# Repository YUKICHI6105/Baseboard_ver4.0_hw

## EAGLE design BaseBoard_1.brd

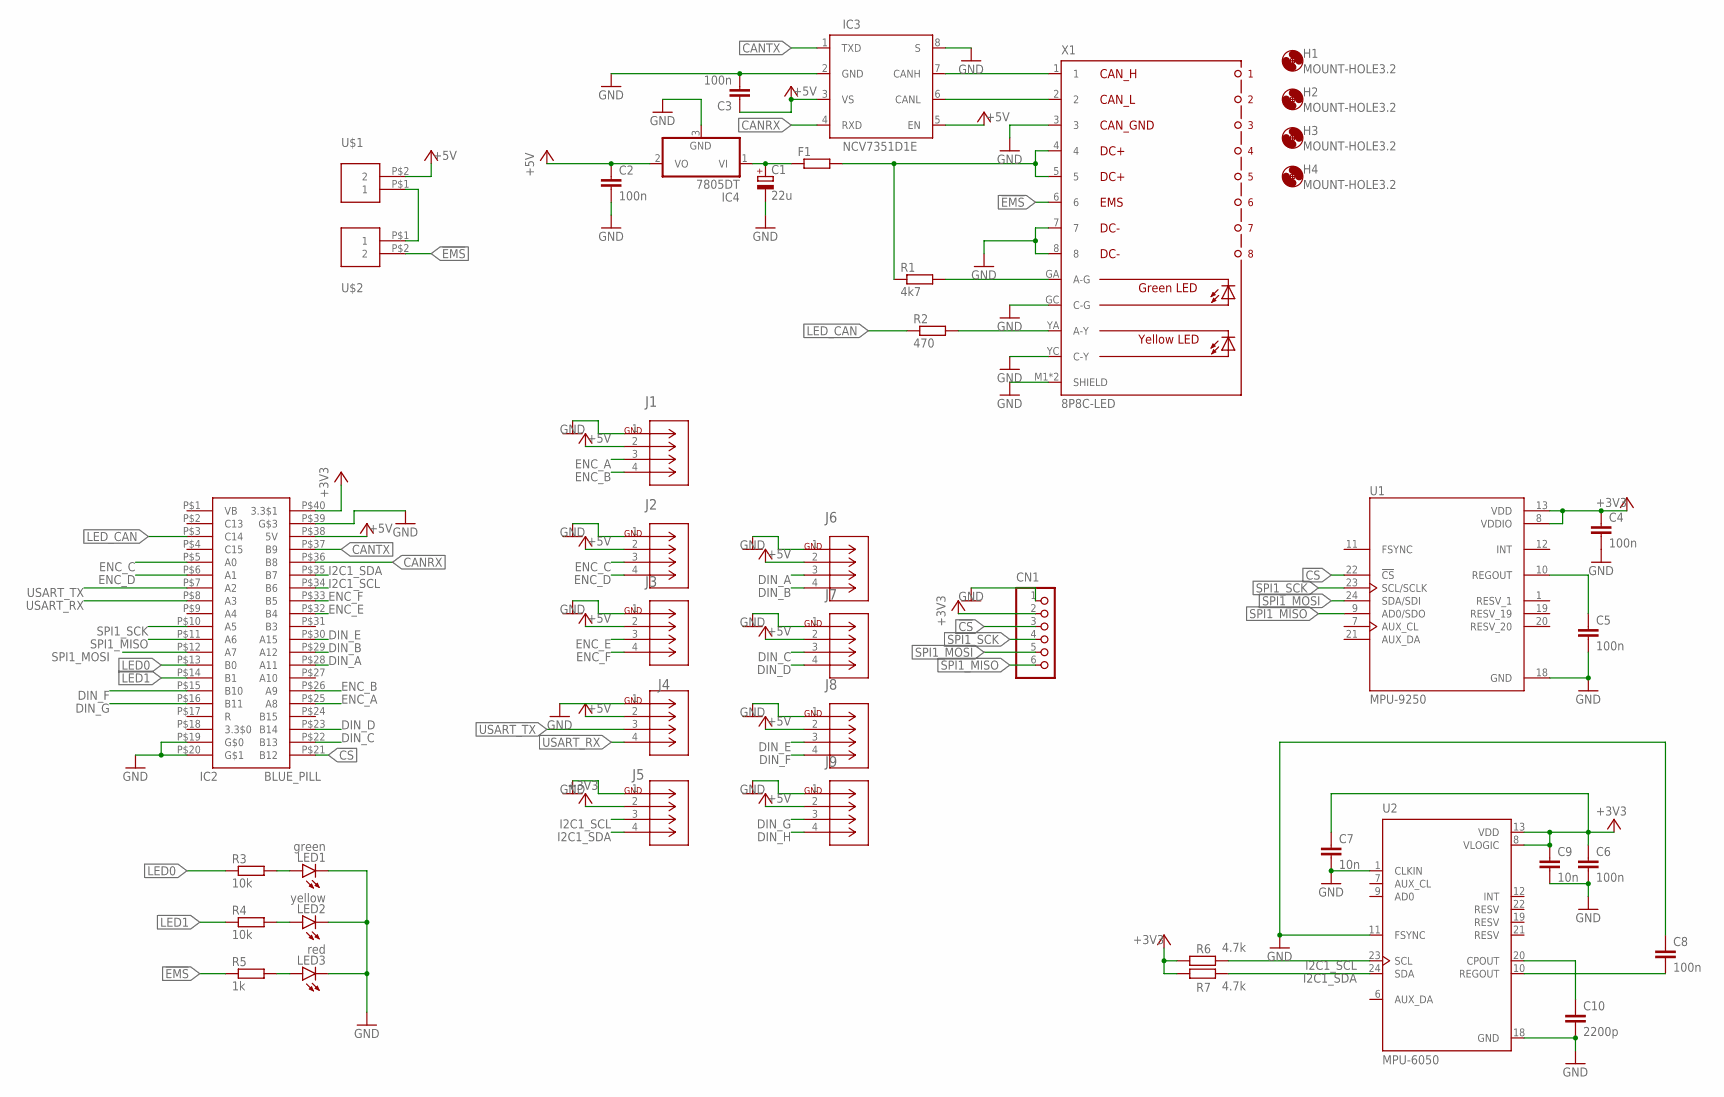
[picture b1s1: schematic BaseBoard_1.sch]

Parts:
C1: 22u; E2,5-5
C2, C3, C4, C5, C6, C8: 100n; C0603
C7, C9: 10n; C0603
C10: 2200p; C0603
CN1: S6B-XH-A
F1: R-EU_R1206; R1206
H1, H2, H3, H4: MOUNT-HOLE3.2; 3,2
IC2: BLUE_PILL
IC3: NCV7351D1E; SO08
IC4: 7805DT; TO252
J1, J2, J3, J4, J5, J6, J7, J8, J9: EP2.5-4-SIDE; CONN4_1744426-4
LED1: green; CHIPLED_0805
LED2: yellow; CHIPLED_0805
LED3: red; CHIPLED_0805
R1: 4k7; R0603
R2: 470; R0603
R3, R4: 10k; R0603
R5: 1k; R0603
R6, R7: 4.7k; R0603
U1: MPU-9250; QFN40P300X300X105-24N
U2: MPU-6050; QFN50P400X400X95-24N
U$1, U$2: XH-2-STRAIGHT; CON-XH-2-STRAIGHT
X1: 8P8C-LED

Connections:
!CS: CN1.3, IC2.P$21 (B12), U1.22 (!CS)
!EMS: R5.1, U$2.P$2 (2), X1.6
+3V3: C4.1, C6.1, C7.1, C9.1, CN1.2, IC2.P$40 (3.3$1), J5.2, R6.1, R7.1, U1.8 (VDDIO), U1.13 (VDD), U2.8 (VLOGIC), U2.13 (VDD)
+5V: C2.1, C3.1, IC2.P$38 (5V), IC3.3 (VS), IC3.5 (EN), IC4.2 (VO), J1.2, J2.2, J3.2, J4.2, J6.2, J7.2, J8.2, J9.2, U$1.P$2 (2)
CANRX: IC2.P$36 (B8), IC3.4 (RXD)
CANTX: IC2.P$37 (B9), IC3.1 (TXD)
DIN_A: IC2.P$28 (A11), J6.3
DIN_B: IC2.P$29 (A12), J6.4
DIN_C: IC2.P$22 (B13), J7.3
DIN_D: IC2.P$23 (B14), J7.4
DIN_E: IC2.P$30 (A15), J8.3
DIN_F: IC2.P$15 (B10), J8.4
DIN_G: IC2.P$16 (B11), J9.3
DIN_H: J9.4
ENC_A: IC2.P$25 (A8), J1.3
ENC_B: IC2.P$26 (A9), J1.4
ENC_C: IC2.P$5 (A0), J2.3
ENC_D: IC2.P$6 (A1), J2.4
ENC_E: IC2.P$32 (B4), J3.3
ENC_F: IC2.P$33 (B5), J3.4
GND: C1.-, C2.2, C3.2, C4.2, C5.2, C6.2, C7.2, C8.1, C9.2, C10.2, CN1.1, IC2.P$19, IC2.P$20, IC2.P$39, IC3.2 (GND), IC3.8 (S), IC4.3 (GND), J1.1, J2.1, J3.1, J4.1, J5.1, J6.1, J7.1, J8.1, J9.1, LED1.C, LED2.C, LED3.C, U1.18 (GND), U2.1 (CLKIN), U2.11 (FSYNC), U2.18 (GND), X1.3, X1.7, X1.8, X1.GC (C-G), X1.M1 (SHIELD), X1.M2 (SHIELD), X1.YC (C-Y)
I2C1_SCL: IC2.P$34 (B6), J5.3, R6.2, U2.23 (SCL)
I2C1_SDA: IC2.P$35 (B7), J5.4, R7.2, U2.24 (SDA)
LED0: IC2.P$13 (B0), R3.1
LED1: IC2.P$14 (B1), R4.1
LED_CAN: IC2.P$3 (C14), R2.1
unnamed: R1.2, X1.GA (A-G)
unnamed: F1.2, R1.1, X1.4, X1.5
unnamed: C1.+, F1.1, IC4.1 (VI)
unnamed: IC3.7 (CANH), X1.1
unnamed: IC3.6 (CANL), X1.2
unnamed: C8.2, U2.10 (REGOUT)
unnamed: C10.1, U2.20 (CPOUT)
unnamed: R2.2, X1.YA (A-Y)
unnamed: U$1.P$1 (1), U$2.P$1 (1)
unnamed: LED1.A, R3.2
unnamed: LED2.A, R4.2
unnamed: LED3.A, R5.2
unnamed: C5.1, U1.10 (REGOUT)
SPI1_MISO: CN1.6, IC2.P$11 (A6), U1.9 (AD0/SDO)
SPI1_MOSI: CN1.5, IC2.P$12 (A7), U1.24 (SDA/SDI)
SPI1_SCK: CN1.4, IC2.P$10 (A5), U1.23 (SCL/SCLK)
USART_RX: IC2.P$8 (A3), J4.4
USART_TX: IC2.P$7 (A2), J4.3

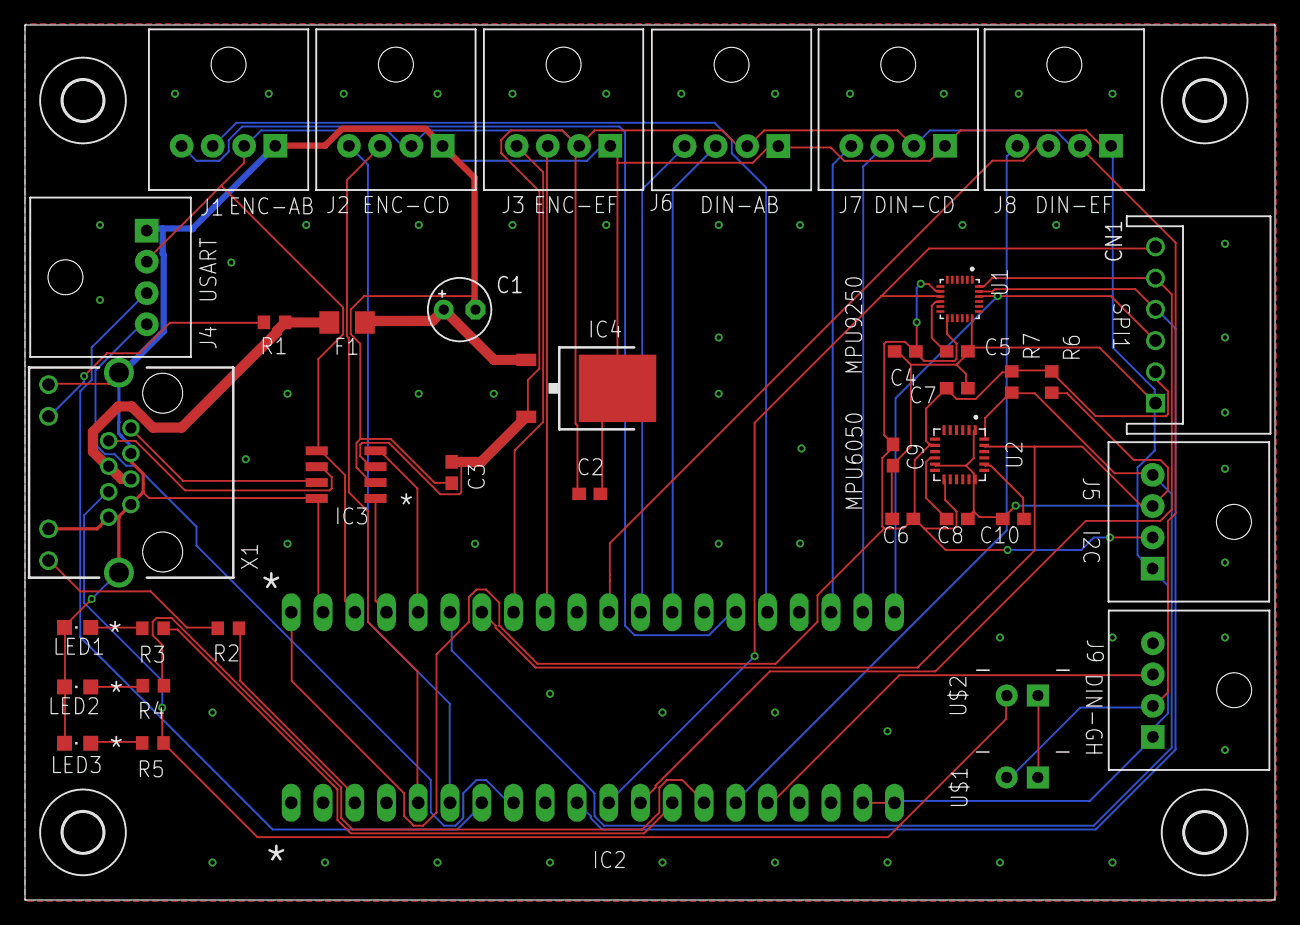
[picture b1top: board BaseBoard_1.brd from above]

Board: 2 copper layers, 100.0 x 70.0 mm, 43 parts (0 on the bottom side), 43 nets.

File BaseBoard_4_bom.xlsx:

Column1 | Column2 | Column3 | Column4 | Column5 | Column6 | Column7 | Column8 | Column9 | Column10 | Column11 | Column12 | Column13 | Column14 | Column15 | Column16 | Column17 | Column18 | Column19
Part | Value | Device | Package | Description | AVAILABILITY | DESCRIPTION | MANUFACTURER_PART_NUMBER | MF | MP | MPN | OC_FARNELL | OC_NEWARK | PACKAGE | PRICE | PURCHASE-URL | SPICEPREFIX | VENDOR
C1 | 22u | CPOL-EUE2.5-5 | E2,5-5 | POLARIZED CAPACITOR, European symbol |  |  |  |  |  |  |  |  |  |  |  | C
C2 | 100n | C-EUC0603 | C0603 | CAPACITOR, European symbol |  |  |  |  |  |  |  |  |  |  |  | C
C3 | 100n | C-EUC0603 | C0603 | CAPACITOR, European symbol |  |  |  |  |  |  |  |  |  |  |  | C
C4 | 100n | C-EUC0603 | C0603 | CAPACITOR, European symbol |  |  |  |  |  |  |  |  |  |  |  | C
C5 | 100n | C-EUC0603 | C0603 | CAPACITOR, European symbol |  |  |  |  |  |  |  |  |  |  |  | C
C6 | 100n | C-EUC0603 | C0603 | CAPACITOR, European symbol |  |  |  |  |  |  |  |  |  |  |  | C
C7 | 10n | C-EUC0603 | C0603 | CAPACITOR, European symbol |  |  |  |  |  |  |  |  |  |  |  | C
C8 | 100n | C-EUC0603 | C0603 | CAPACITOR, European symbol |  |  |  |  |  |  |  |  |  |  |  | C
C9 | 10n | C-EUC0603 | C0603 | CAPACITOR, European symbol |  |  |  |  |  |  |  |  |  |  |  | C
C10 | 2200p | C-EUC0603 | C0603 | CAPACITOR, European symbol |  |  |  |  |  |  |  |  |  |  |  | C
CN1 |  | S6B-XH-A | S6B-XH-A | Wire-to-Board 2.5mm pitch side mount connector
F1 |  | R-EU_R1206 | R1206 | RESISTOR, European symbol |  |  |  |  |  |  |  |  |  |  |  | R
H1 | MOUNT-HOLE3.2 | MOUNT-HOLE3.2 | 3,2 | MOUNTING HOLE with drill center marker
H2 | MOUNT-HOLE3.2 | MOUNT-HOLE3.2 | 3,2 | MOUNTING HOLE with drill center marker
H3 | MOUNT-HOLE3.2 | MOUNT-HOLE3.2 | 3,2 | MOUNTING HOLE with drill center marker
H4 | MOUNT-HOLE3.2 | MOUNT-HOLE3.2 | 3,2 | MOUNTING HOLE with drill center marker
IC2 | BLUE_PILL | BLUE_PILL | BLUE_PILL
IC3 | NCV7351D1E | NCV7351D1E | SO08 | High Speed CAN Transceiver
IC4 | 7805DT | 7805DT | TO252 | Positive VOLTAGE REGULATOR
J1 | EP2.5-4-SIDE | EP2.5-4-SIDE | CONN4_1744426-4 |  |  |  | 17444264 |  |  |  |  |  |  |  |  |  | TE Connectivity
J2 | EP2.5-4-SIDE | EP2.5-4-SIDE | CONN4_1744426-4 |  |  |  | 17444264 |  |  |  |  |  |  |  |  |  | TE Connectivity
J3 | EP2.5-4-SIDE | EP2.5-4-SIDE | CONN4_1744426-4 |  |  |  | 17444264 |  |  |  |  |  |  |  |  |  | TE Connectivity
J4 | EP2.5-4-SIDE | EP2.5-4-SIDE | CONN4_1744426-4 |  |  |  | 17444264 |  |  |  |  |  |  |  |  |  | TE Connectivity
J5 | EP2.5-4-SIDE | EP2.5-4-SIDE | CONN4_1744426-4 |  |  |  | 17444264 |  |  |  |  |  |  |  |  |  | TE Connectivity
J6 | EP2.5-4-SIDE | EP2.5-4-SIDE | CONN4_1744426-4 |  |  |  | 17444264 |  |  |  |  |  |  |  |  |  | TE Connectivity
J7 | EP2.5-4-SIDE | EP2.5-4-SIDE | CONN4_1744426-4 |  |  |  | 17444264 |  |  |  |  |  |  |  |  |  | TE Connectivity
J8 | EP2.5-4-SIDE | EP2.5-4-SIDE | CONN4_1744426-4 |  |  |  | 17444264 |  |  |  |  |  |  |  |  |  | TE Connectivity
J9 | EP2.5-4-SIDE | EP2.5-4-SIDE | CONN4_1744426-4 |  |  |  | 17444264 |  |  |  |  |  |  |  |  |  | TE Connectivity
LED1 | green | LEDCHIPLED_0805 | CHIPLED_0805 | LED
LED2 | yellow | LEDCHIPLED_0805 | CHIPLED_0805 | LED
LED3 | red | LEDCHIPLED_0805 | CHIPLED_0805 | LED
R1 | 4k7 | R-EU_R0603 | R0603 | RESISTOR, European symbol |  |  |  |  |  |  |  |  |  |  |  | R
R2 | 470 | R-EU_R0603 | R0603 | RESISTOR, European symbol |  |  |  |  |  |  |  |  |  |  |  | R
R3 | 10k | R-EU_R0603 | R0603 | RESISTOR, European symbol |  |  |  |  |  |  |  |  |  |  |  | R
R4 | 10k | R-EU_R0603 | R0603 | RESISTOR, European symbol |  |  |  |  |  |  |  |  |  |  |  | R
R5 | 1k | R-EU_R0603 | R0603 | RESISTOR, European symbol |  |  |  |  |  |  |  |  |  |  |  | R
R6 | 4.7k | R-EU_R0603 | R0603 | RESISTOR, European symbol |  |  |  |  |  |  |  |  |  |  |  | R
R7 | 4.7k | R-EU_R0603 | R0603 | RESISTOR, European symbol |  |  |  |  |  |  |  |  |  |  |  | R
U$1 | XH-2-STRAIGHT | XH-2-STRAIGHT | CON-XH-2-STRAIGHT
U$2 | XH-2-STRAIGHT | XH-2-STRAIGHT | CON-XH-2-STRAIGHT
U1 | MPU-9250 | MPU-9250 | QFN40P300X300X105-24N | Axis=3 Axis Gyro+3 Axis Accel+Compass. Pin For Pin With m | Unavailable | SMD Gyroscope/Accelerometer/Magnetometer Sensor | 9-AXIS |  | TDK InvenSense | MPU-9250 |  |  |  | QFN-24 TDK InvenSense | None
U2 | MPU-6050 | MPU-6050 | QFN50P400X400X95-24N | MPU-6050 Six-Axis (Gyro + Accelerometer) MEMS MotionTracking・・｢ Devices Check a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 | In Stock | MPU-6050 series Accelerometer, Gyroscope, 3 Axis Sensor Evaluation Board |  | TDK InvenSense | MPU-6050 |  |  |  | VFQFN-24 TDK InvenSense | None | https://pricing.snapeda.com/search/part/MPU-6050/?ref=eda
X1 | 8P8C-LED | 8P8C-LED | 8P8C-LED | generic 8P8C connector with two LED's |  |  |  |  |  |  | unknown | unknown
